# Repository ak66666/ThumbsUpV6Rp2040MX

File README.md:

# ThumbsUp! v6 RP2040-based keyboard for MX and ALPS switches

Multilevel 44 Key Split Contoured Keyboard.
2-key Thumb Cluster
   
* RP2040 is soldered on the boards.
* TRS (3-wire) audio cable to connect the halves.
* Hot swap sockets for MX switches, the ALPS need to be soldered in.
* USB-C connectors.
* Connects to computer from either side, halves could be used separately.

Board needs 3D printed switch plates: https://github.com/ak66666/ThubmsUpSwitchPlates

Other pictures in Photos folder.

# Firmware

Please refer to this article:
https://thumbsupkeyboards.blogspot.com/2024/02/source-files-and-default-firmware.html

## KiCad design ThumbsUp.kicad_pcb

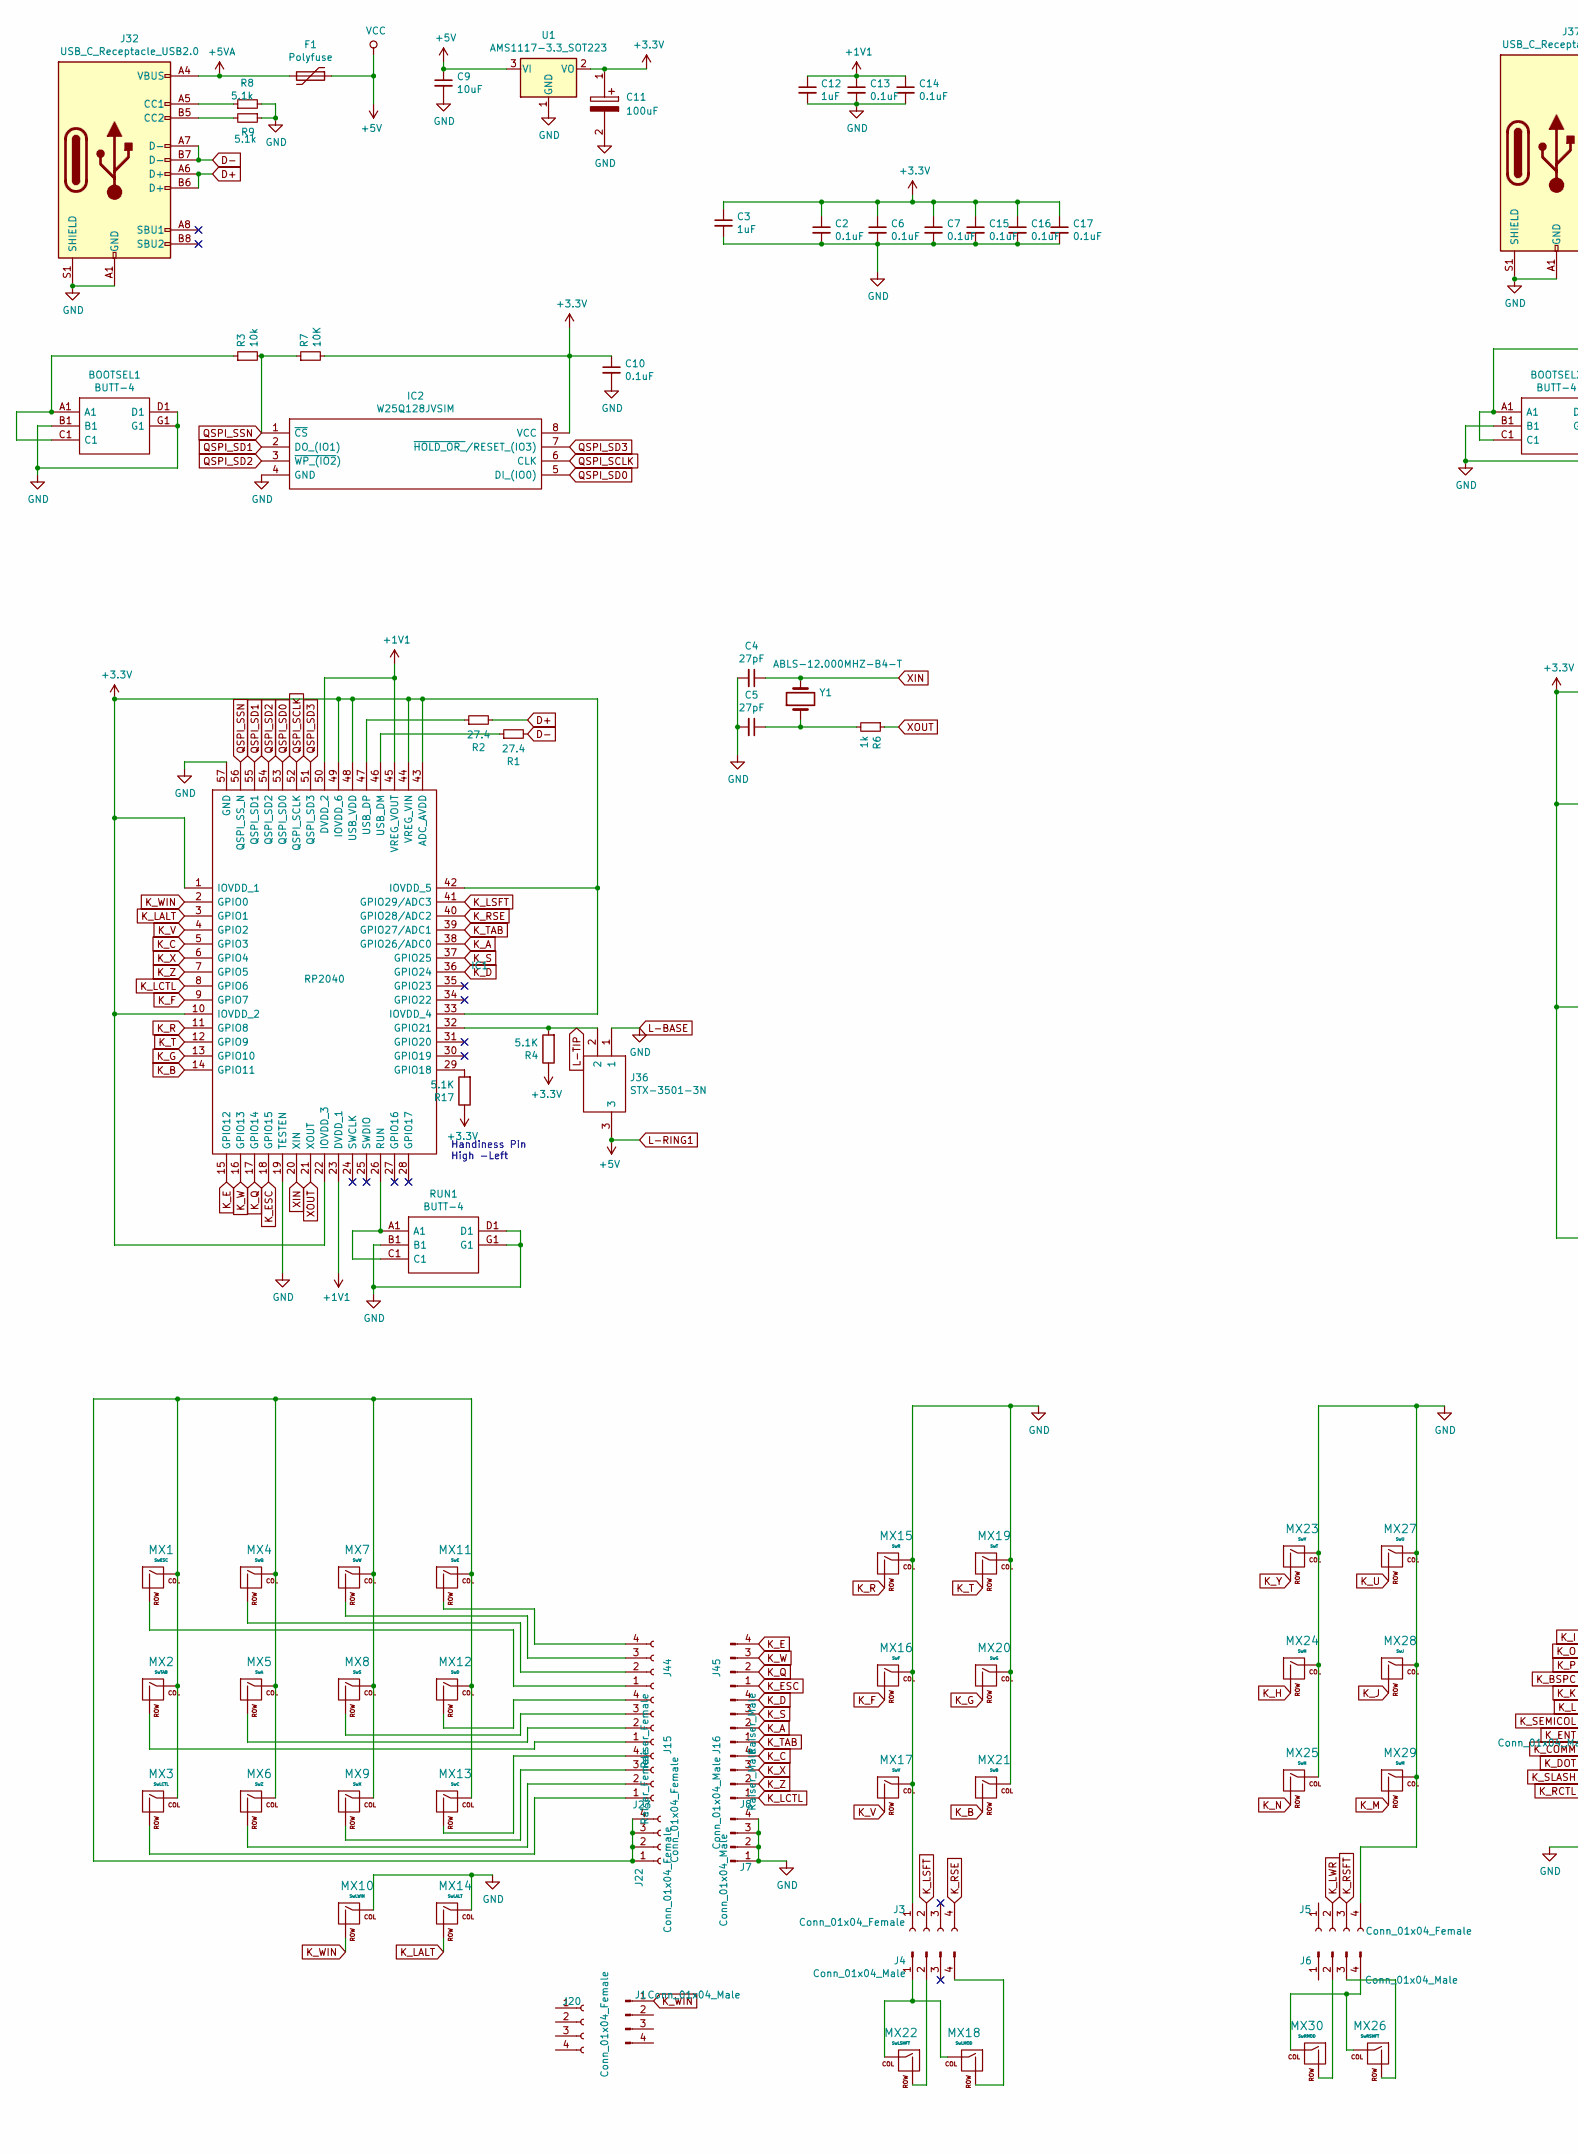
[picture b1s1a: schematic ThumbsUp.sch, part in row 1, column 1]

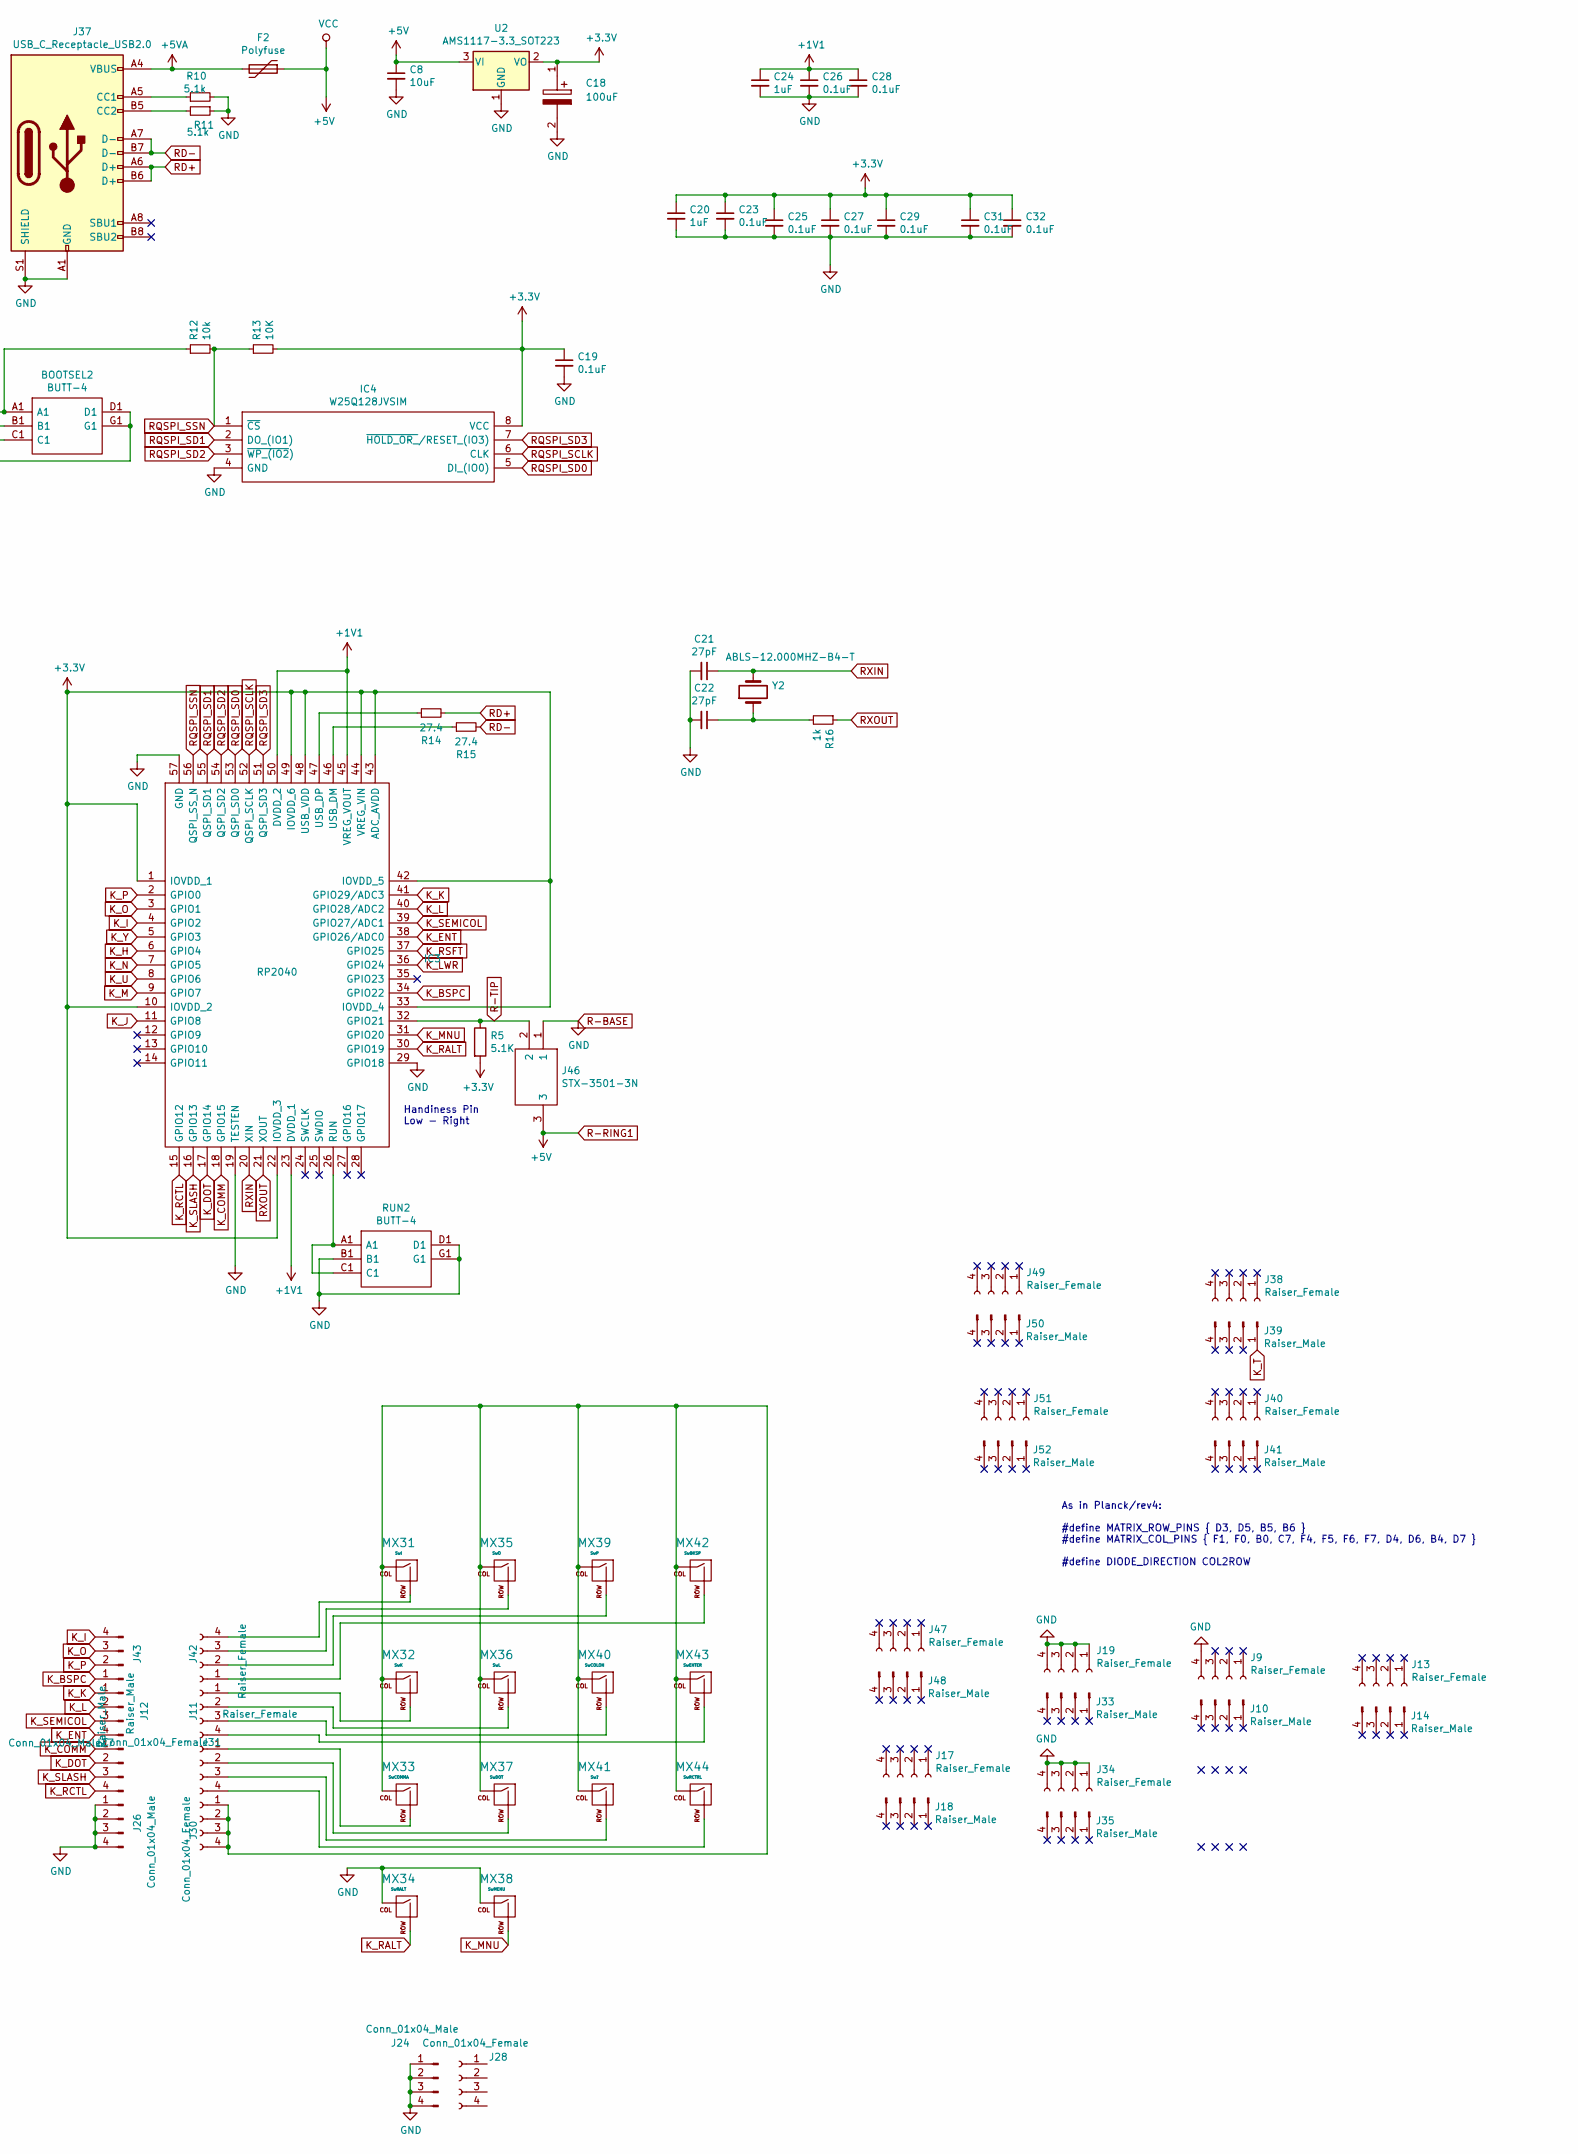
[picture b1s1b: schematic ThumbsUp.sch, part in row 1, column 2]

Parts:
BOOTSEL1, BOOTSEL2: BUTT-4; BUTT4; Manufacturer_Part_Number BUTT-4; Mouser Part Number 992-BUTT-4
C2, C6, C7, C10, C13, C14, C15, C16, C17, C19, C23, C25, C26, C27, C28, C29, C31, C32: 0.1uF; C_0402_1005Metric
C3, C12, C20, C24: 1uF; C_0402_1005Metric
C4, C5, C21, C22: 27pF; C_0402_1005Metric
C8, C9: 10uF; C_0402_1005Metric
C11, C18: 100uF; C_1210_3225Metric
F1, F2: Polyfuse; Fuse_1206_3216Metric
IC1, IC3: RP2040; RP2040-QFN-56; Manufacturer_Part_Number RP2040
IC2, IC4: W25Q128JVSIM; SOIC127P790X216-8N; Manufacturer_Part_Number W25Q128JVSIM; Mouser Part Number 454-W25Q128JVSIM
J1, J4, J6, J7, J8, J24, J26, J27: Conn_01x04_Male; PinHeader_1x04_P2.54mm_Vertical
J3, J5, J20, J22, J23, J28, J30, J31: Conn_01x04_Female; PinSocket_1x04_P2.54mm_Vertical
J9, J11, J13, J15, J17, J19, J34, J38, J40, J42, J44, J47, J49, J51: Raiser_Female; PinSocket_1x04_P2.54mm_Vertical
J10, J12, J14, J16, J18, J33, J35, J39, J41, J43, J45, J48, J50, J52: Raiser_Male; PinHeader_1x04_P2.54mm_Vertical
J32, J37: USB_C_Receptacle_USB2.0; USB_C_Receptacle_Palconn_UTC16-G
J36, J46: STX-3501-3N; STX35013N; Manufacturer_Part_Number STX-3501-3N; Mouser Part Number 806-STX-3501-3N
MX1: SwESC; MX-1U-NoLED_HotSwap
MX2: SwTAB; MX-1U-NoLED_HotSwap
MX3: SwLCTL; MX-1U-NoLED_HotSwap
MX4: SwQ; MX-1U-NoLED_HotSwap
MX5: SwA; MX-1U-NoLED_HotSwap
MX6: SwZ; MX-1U-NoLED_HotSwap
MX7: SwW; MX-1U-NoLED_HotSwap
MX8: SwS; MX-1U-NoLED_HotSwap
MX9: SwX; MX-1U-NoLED_HotSwap
MX10: SwLWIN; MX-1U-NoLED_HotSwap
MX11: SwE; MX-1U-NoLED_HotSwap
MX12: SwD; MX-1U-NoLED_HotSwap
MX13: SwC; MX-1U-NoLED_HotSwap
MX14: SwLALT; MX-1U-NoLED_HotSwap
MX15: SwR; MX-1U-NoLED_HotSwap
MX16: SwF; MX-1U-NoLED_HotSwap
MX17: SwV; MX-1U-NoLED_HotSwap
MX18: SwLMOD; MX-1U-NoLED_HotSwap
MX19: SwT; MX-1U-NoLED_HotSwap
MX20: SwG; MX-1U-NoLED_HotSwap
MX21: SwB; MX-1U-NoLED_HotSwap
MX22: SwLSHFT; MX-1U-NoLED_HotSwap
MX23: SwY; MX-1U-NoLED_HotSwap
MX24: SwH; MX-1U-NoLED_HotSwap
MX25: SwN; MX-1U-NoLED_HotSwap
MX26: SwRSHFT; MX-1U-NoLED_HotSwap
MX27: SwU; MX-1U-NoLED_HotSwap
MX28: SwJ; MX-1U-NoLED_HotSwap
MX29: SwM; MX-1U-NoLED_HotSwap
MX30: SwRMOD; MX-1U-NoLED_HotSwap
MX31: SwI; MX-1U-NoLED_HotSwap
MX32: SwK; MX-1U-NoLED_HotSwap
MX33: SwCOMMA; MX-1U-NoLED_HotSwap
MX34: SwRALT; MX-1U-NoLED_HotSwap
MX35: SwO; MX-1U-NoLED_HotSwap
MX36: SwL; MX-1U-NoLED_HotSwap
MX37: SwDOT; MX-1U-NoLED_HotSwap
MX38: SwMENU; MX-1U-NoLED_HotSwap
MX39: SwP; MX-1U-NoLED_HotSwap
MX40: SwCOLON; MX-1U-NoLED_HotSwap
MX41: Sw?; MX-1U-NoLED_HotSwap
MX42: SwBKSP; MX-1U-NoLED_HotSwap
MX43: SwENTER; MX-1U-NoLED_HotSwap
MX44: SwRCTRL; MX-1U-NoLED_HotSwap
R1, R2, R14, R15: 27.4; R_0402_1005Metric
R3, R12: 10k; R_0402_1005Metric
R4, R5, R17: 5.1K; R_0402_1005Metric
R6, R16: 1k; R_0402_1005Metric
R7, R13: 10K; R_0402_1005Metric
R8, R9, R10, R11: 5.1k; R_0402_1005Metric
RUN1, RUN2: BUTT-4; BUTT4; Manufacturer_Part_Number BUTT-4; Mouser Part Number 992-BUTT-4
U1, U2: AMS1117-3.3_SOT223; SOT229P700X180-4N
Y1, Y2: ABLS-12.000MHZ-B4-T; HC%2f49US-(AT49)_1

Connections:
+1V1: C12.1, C13.1, C14.1, C24.1, C26.1, C28.1, IC1.23 (DVDD_1), IC1.45 (VREG_VOUT), IC1.50 (DVDD_2), IC3.23 (DVDD_1), IC3.45 (VREG_VOUT), IC3.50 (DVDD_2)
+3V3: C2.1, C3.1, C6.1, C7.1, C10.1, C11.1, C15.1, C16.1, C17.1, C18.1, C19.1, C20.1, C23.1, C25.1, C27.1, C29.1, C31.1, C32.1, IC1.1 (IOVDD_1), IC1.10 (IOVDD_2), IC1.22 (IOVDD_3), IC1.33 (IOVDD_4), IC1.42 (IOVDD_5), IC1.43 (ADC_AVDD), IC1.44 (VREG_VIN), IC1.48 (USB_VDD), IC1.49 (IOVDD_6), IC2.8 (VCC), IC3.1 (IOVDD_1), IC3.10 (IOVDD_2), IC3.22 (IOVDD_3), IC3.33 (IOVDD_4), IC3.42 (IOVDD_5), IC3.43 (ADC_AVDD), IC3.44 (VREG_VIN), IC3.48 (USB_VDD), IC3.49 (IOVDD_6), IC4.8 (VCC), R4.1, R5.2, R7.2, R13.2, R17.1, U1.2 (VO), U2.2 (VO)
+5VA: F1.2, F2.2, J32.A4 (VBUS), J32.A9 (VBUS), J32.B4 (VBUS), J32.B9 (VBUS), J37.A4 (VBUS), J37.A9 (VBUS), J37.B4 (VBUS), J37.B9 (VBUS)
D+: J32.A6 (D+), J32.B6 (D+), R2.2
D-: J32.A7 (D-), J32.B7 (D-), R1.2
K_A: IC1.38 (GPIO26/ADC0), J16.2
K_B: IC1.14 (GPIO11), MX21.2 (ROW)
K_BSPC: IC3.34 (GPIO22), J43.1
K_C: IC1.5 (GPIO3), J8.4
K_COMM: IC3.18 (GPIO15), J27.1
K_D: IC1.36 (GPIO24), J16.4
K_DOT: IC3.17 (GPIO14), J27.2
K_E: IC1.15 (GPIO12), J45.4
K_ENT: IC3.38 (GPIO26/ADC0), J12.4
K_ESC: IC1.18 (GPIO15), J45.1
K_F: IC1.9 (GPIO7), MX16.2 (ROW)
K_G: IC1.13 (GPIO10), MX20.2 (ROW)
K_H: IC3.6 (GPIO4), MX24.2 (ROW)
K_I: IC3.4 (GPIO2), J43.4
K_J: IC3.11 (GPIO8), MX28.2 (ROW)
K_K: IC3.41 (GPIO29/ADC3), J12.1
K_L: IC3.40 (GPIO28/ADC2), J12.2
K_LALT: IC1.3 (GPIO1), MX14.2 (ROW)
K_LCTL: IC1.8 (GPIO6), J8.1
K_LSFT: IC1.41 (GPIO29/ADC3), J3.2
K_LWR: IC3.36 (GPIO24), J5.2
K_M: IC3.9 (GPIO7), MX29.2 (ROW)
K_MNU: IC3.31 (GPIO20), MX38.2 (ROW)
K_N: IC3.7 (GPIO5), MX25.2 (ROW)
K_O: IC3.3 (GPIO1), J43.3
K_P: IC3.2 (GPIO0), J43.2
K_Q: IC1.17 (GPIO14), J45.2
K_R: IC1.11 (GPIO8), MX15.2 (ROW)
K_RALT: IC3.30 (GPIO19), MX34.2 (ROW)
K_RCTL: IC3.15 (GPIO12), J27.4
K_RSE: IC1.40 (GPIO28/ADC2), J3.4
K_RSFT: IC3.37 (GPIO25), J5.3
K_S: IC1.37 (GPIO25), J16.3
K_SEMICOL: IC3.39 (GPIO27/ADC1), J12.3
K_SLASH: IC3.16 (GPIO13), J27.3
K_T: IC1.12 (GPIO9), J39.1, MX19.2 (ROW)
K_TAB: IC1.39 (GPIO27/ADC1), J16.1
K_U: IC3.8 (GPIO6), MX27.2 (ROW)
K_V: IC1.4 (GPIO2), MX17.2 (ROW)
K_W: IC1.16 (GPIO13), J45.3
K_WIN: IC1.2 (GPIO0), J1.1, MX10.2 (ROW)
K_X: IC1.6 (GPIO4), J8.3
K_Y: IC3.5 (GPIO3), MX23.2 (ROW)
K_Z: IC1.7 (GPIO5), J8.2
L-BASE: BOOTSEL1.B1, BOOTSEL1.D1, BOOTSEL1.G1, BOOTSEL2.B1, BOOTSEL2.D1, BOOTSEL2.G1, C2.2, C3.2, C4.2, C5.2, C6.2, C7.2, C8.2, C9.2, C10.2, C11.2, C12.2, C13.2, C14.2, C15.2, C16.2, C17.2, C18.2, C19.2, C20.2, C21.2, C22.2, C23.2, C24.2, C25.2, C26.2, C27.2, C28.2, C29.2, C31.2, C32.2, IC1.19 (TESTEN), IC1.57 (GND), IC2.4 (GND), IC3.19 (TESTEN), IC3.29 (GPIO18), IC3.57 (GND), IC4.4 (GND), J3.1, J5.4, J7.1, J7.2, J7.3, J7.4, J9.4, J19.1, J19.2, J19.3, J19.4, J24.1, J24.2, J24.3, J24.4, J26.1, J26.2, J26.3, J26.4, J32.A1 (GND), J32.A12 (GND), J32.B1 (GND), J32.B12 (GND), J32.S1 (SHIELD), J34.1, J34.2, J34.3, J34.4, J36.1, J37.A1 (GND), J37.A12 (GND), J37.B1 (GND), J37.B12 (GND), J37.S1 (SHIELD), J46.1, MX10.1 (COL), MX14.1 (COL), MX15.1 (COL), MX16.1 (COL), MX17.1 (COL), MX19.1 (COL), MX20.1 (COL), MX21.1 (COL), MX23.1 (COL), MX24.1 (COL), MX25.1 (COL), MX27.1 (COL), MX28.1 (COL), MX29.1 (COL), MX34.1 (COL), MX38.1 (COL), R8.2, R9.1, R10.2, R11.1, RUN1.B1, RUN1.D1, RUN1.G1, RUN2.B1, RUN2.D1, RUN2.G1, U1.1 (GND), U2.1 (GND)
L-RING1: C8.1, C9.1, F1.1, F2.1, J36.3, J46.3, U1.3 (VI), U2.3 (VI)
L-TIP: IC1.32 (GPIO21), J36.2, R4.2
unnamed: BOOTSEL1.A1, BOOTSEL1.C1, R3.1
unnamed: BOOTSEL2.A1, BOOTSEL2.C1, R12.1
unnamed: C5.1, R6.2, Y1.1
unnamed: C22.1, R16.2, Y2.1
unnamed: IC1.26 (RUN), RUN1.A1, RUN1.C1
unnamed: IC1.29 (GPIO18), R17.2
unnamed: IC1.46 (USB_DM), R1.1
unnamed: IC1.47 (USB_DP), R2.1
unnamed: IC3.26 (RUN), RUN2.A1, RUN2.C1
unnamed: IC3.46 (USB_DM), R15.1
unnamed: IC3.47 (USB_DP), R14.1
unnamed: J4.1, MX18.1 (COL), MX22.1 (COL)
unnamed: J4.2, MX22.2 (ROW)
unnamed: J4.4, MX18.2 (ROW)
unnamed: J6.2, MX30.2 (ROW)
unnamed: J6.3, MX26.2 (ROW)
unnamed: J6.4, MX26.1 (COL), MX30.1 (COL)
unnamed: J11.1, MX32.2 (ROW)
unnamed: J11.2, MX36.2 (ROW)
unnamed: J11.3, MX40.2 (ROW)
unnamed: J11.4, MX43.2 (ROW)
unnamed: J15.1, MX2.2 (ROW)
unnamed: J15.2, MX5.2 (ROW)
unnamed: J15.3, MX8.2 (ROW)
unnamed: J15.4, MX12.2 (ROW)
unnamed: J22.1, J22.2, J22.3, J22.4, MX1.1 (COL), MX2.1 (COL), MX3.1 (COL), MX4.1 (COL), MX5.1 (COL), MX6.1 (COL), MX7.1 (COL), MX8.1 (COL), MX9.1 (COL), MX11.1 (COL), MX12.1 (COL), MX13.1 (COL)
unnamed: J23.1, MX3.2 (ROW)
unnamed: J23.2, MX6.2 (ROW)
unnamed: J23.3, MX9.2 (ROW)
unnamed: J23.4, MX13.2 (ROW)
unnamed: J30.1, J30.2, J30.3, J30.4, MX31.1 (COL), MX32.1 (COL), MX33.1 (COL), MX35.1 (COL), MX36.1 (COL), MX37.1 (COL), MX39.1 (COL), MX40.1 (COL), MX41.1 (COL), MX42.1 (COL), MX43.1 (COL), MX44.1 (COL)
unnamed: J31.1, MX33.2 (ROW)
unnamed: J31.2, MX37.2 (ROW)
unnamed: J31.3, MX41.2 (ROW)
unnamed: J31.4, MX44.2 (ROW)
unnamed: J32.A5 (CC1), R8.1
unnamed: J32.B5 (CC2), R9.2
unnamed: J37.A5 (CC1), R10.1
unnamed: J37.B5 (CC2), R11.2
unnamed: J42.1, MX42.2 (ROW)
unnamed: J42.2, MX39.2 (ROW)
unnamed: J42.3, MX35.2 (ROW)
unnamed: J42.4, MX31.2 (ROW)
unnamed: J44.1, MX1.2 (ROW)
unnamed: J44.2, MX4.2 (ROW)
unnamed: J44.3, MX7.2 (ROW)
unnamed: J44.4, MX11.2 (ROW)
QSPI_SCLK: IC1.52 (QSPI_SCLK), IC2.6 (CLK)
QSPI_SD0: IC1.53 (QSPI_SD0), IC2.5 (DI_(IO0))
QSPI_SD1: IC1.55 (QSPI_SD1), IC2.2 (DO_(IO1))
QSPI_SD2: IC1.54 (QSPI_SD2), IC2.3 (~WP_(IO2))
QSPI_SD3: IC1.51 (QSPI_SD3), IC2.7 (~HOLD_OR_~/RESET_(IO3))
QSPI_SSN: IC1.56 (QSPI_SS_N), IC2.1 (~CS), R3.2, R7.1
R-TIP: IC3.32 (GPIO21), J46.2, R5.1
RD+: J37.A6 (D+), J37.B6 (D+), R14.2
RD-: J37.A7 (D-), J37.B7 (D-), R15.2
RQSPI_SCLK: IC3.52 (QSPI_SCLK), IC4.6 (CLK)
RQSPI_SD0: IC3.53 (QSPI_SD0), IC4.5 (DI_(IO0))
RQSPI_SD1: IC3.55 (QSPI_SD1), IC4.2 (DO_(IO1))
RQSPI_SD2: IC3.54 (QSPI_SD2), IC4.3 (~WP_(IO2))
RQSPI_SD3: IC3.51 (QSPI_SD3), IC4.7 (~HOLD_OR_~/RESET_(IO3))
RQSPI_SSN: IC3.56 (QSPI_SS_N), IC4.1 (~CS), R12.2, R13.1
RXIN: C21.1, IC3.20 (XIN), Y2.2
RXOUT: IC3.21 (XOUT), R16.1
XIN: C4.1, IC1.20 (XIN), Y1.2
XOUT: IC1.21 (XOUT), R6.1

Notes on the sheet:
As in Planck/rev4: #define MATRIX_ROW_PINS { D3, D5, B5, B6 } #define MATRIX_COL_PINS { F1, F0, B0, C7, F4, F5, F6, F7, D4, D6, B4, D7 } #define DIODE_DIRECTION COL2ROW
Handiness Pin High -Left
Handiness Pin Low - Right

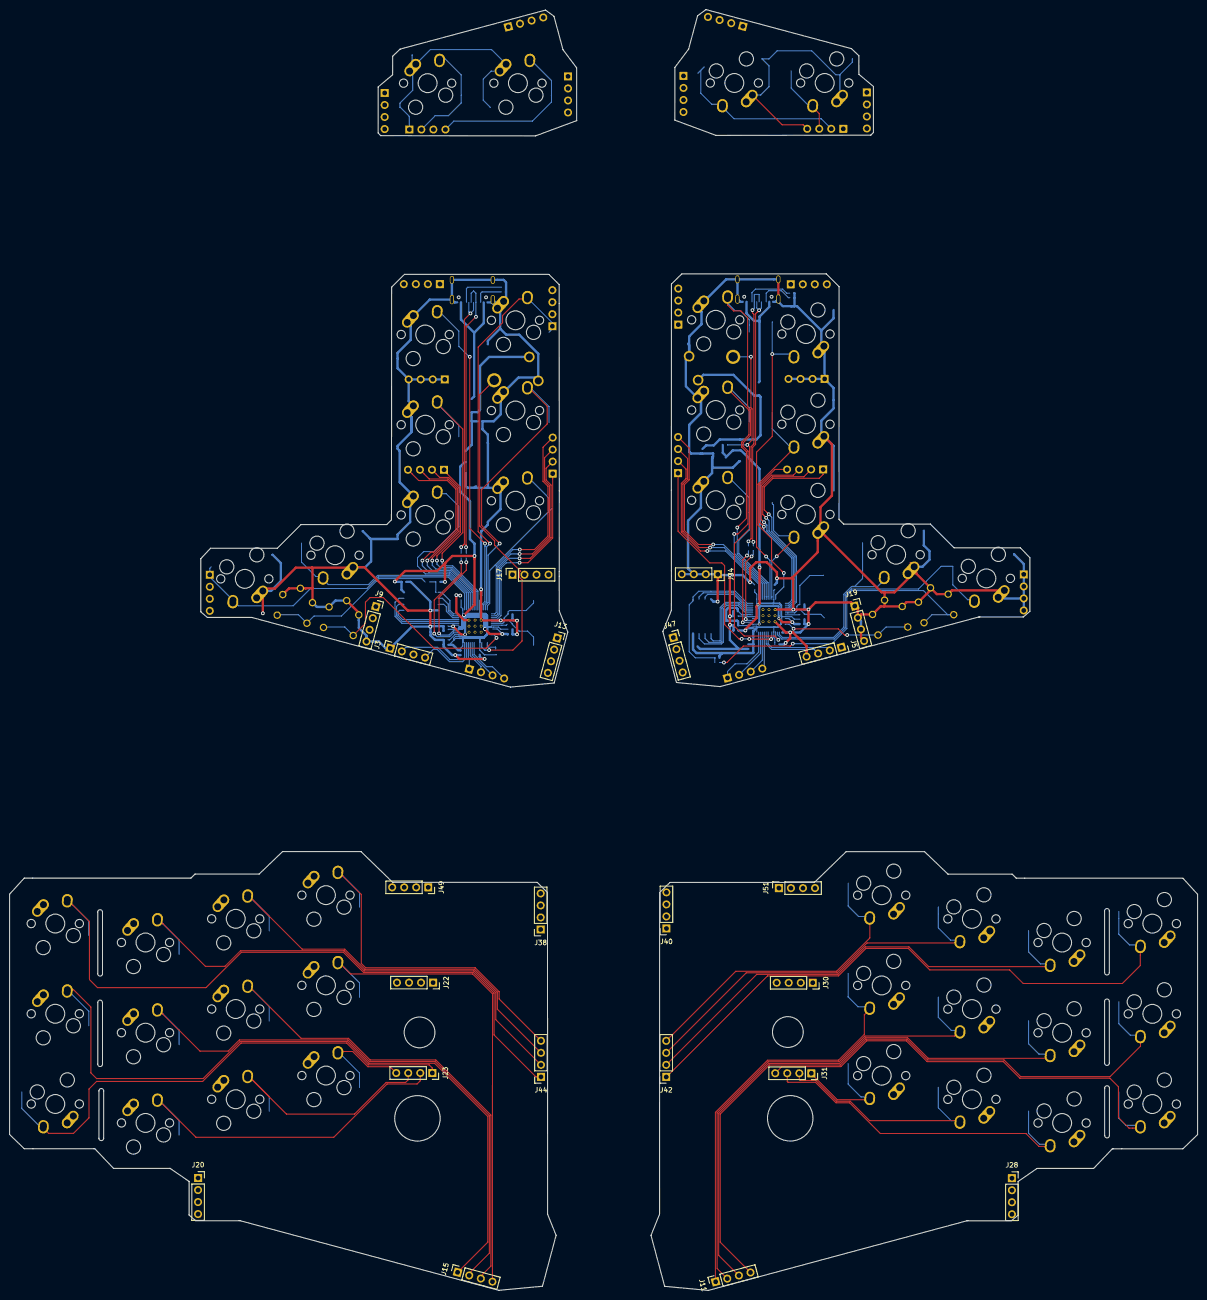
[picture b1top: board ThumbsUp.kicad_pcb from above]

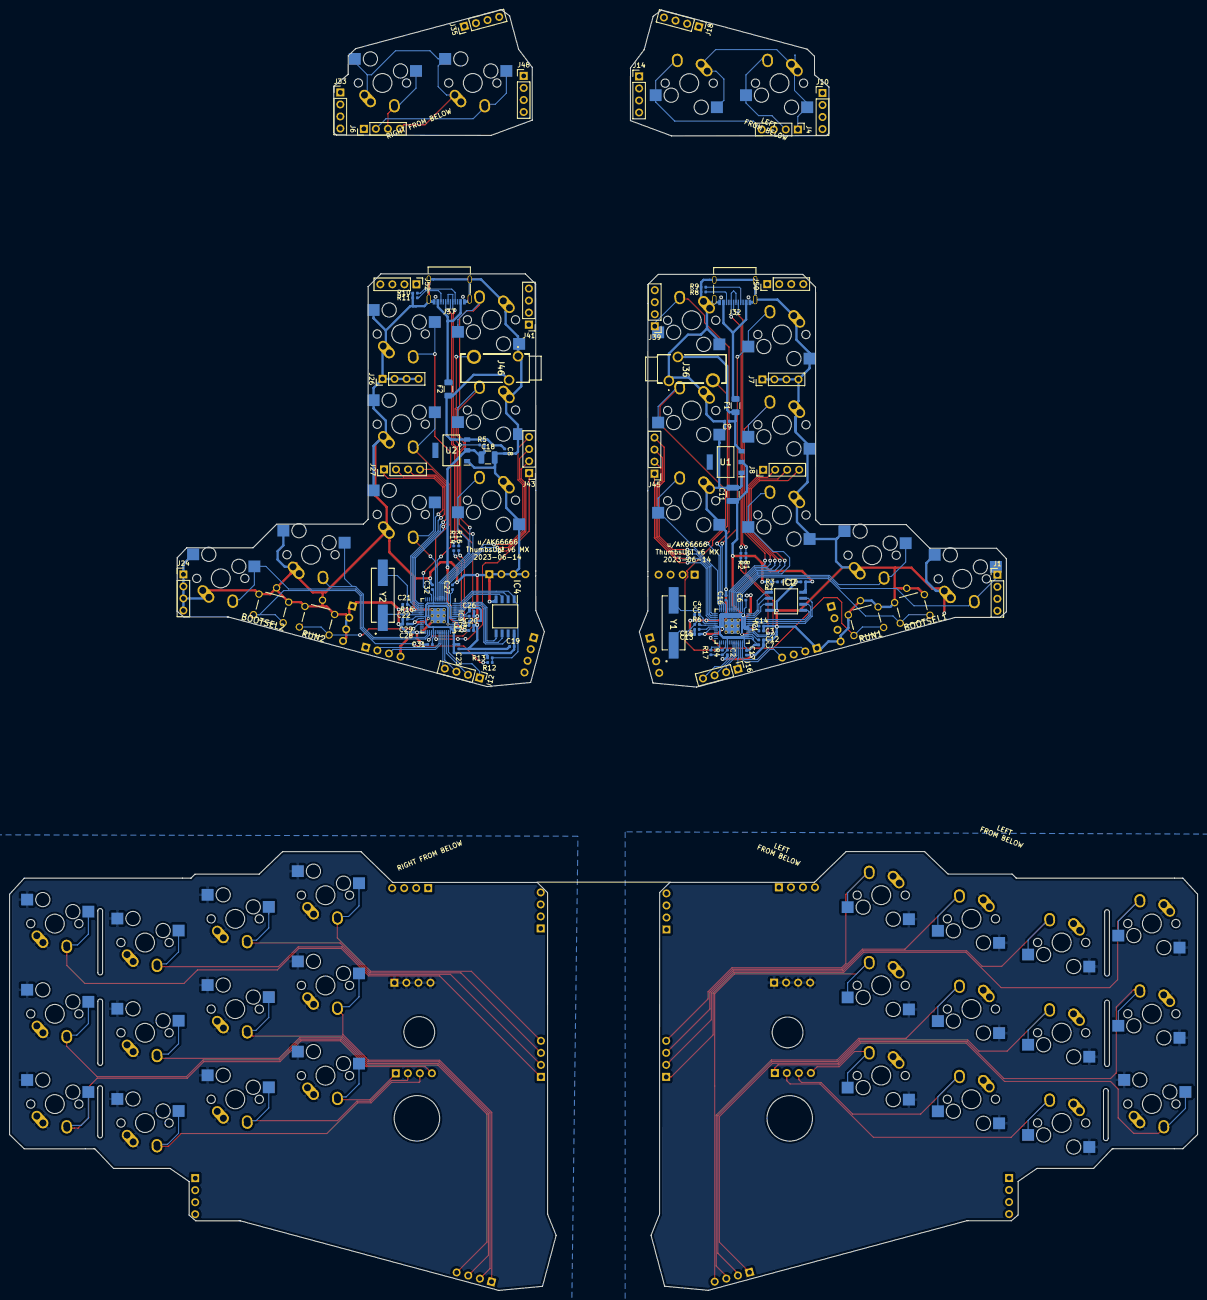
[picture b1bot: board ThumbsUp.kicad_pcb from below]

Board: 2 copper layers, 250.8 x 270.5 mm, 153 parts (87 on the bottom side), 118 nets.

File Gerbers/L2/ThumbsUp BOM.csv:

"Id";"Designator";"Package";"Quantity";"Designation";"Supplier and ref";
1;"G***";"LeavesW311";1;"LOGO";;;
2;"MX20";"MX-1U-NoLED_HotSwap";1;"SwG";;;
3;"U1";"SOT229P700X180-4N";1;"AMS1117-3.3_SOT223";;;
4;"C11";"C_1210_3225Metric";1;"100uF";;;
5;"RUN1,BOOTSEL1";"BUTT4";2;"BUTT-4";;;
6;"R17,R4";"R_0402_1005Metric";2;"5.1K";;;
7;"J50,J39,J45,J16";"PinHeader_1x04_P2.54mm_Vertical";4;"Raiser_Male";;;
8;"MX16";"MX-1U-NoLED_HotSwap";1;"SwF";;;
9;"MX21";"MX-1U-NoLED_HotSwap";1;"SwB";;;
10;"MX19";"MX-1U-NoLED_HotSwap";1;"SwT";;;
11;"MX17";"MX-1U-NoLED_HotSwap";1;"SwV";;;
12;"MX15";"MX-1U-NoLED_HotSwap";1;"SwR";;;
13;"MX14";"MX-1U-NoLED_HotSwap";1;"SwLALT";;;
14;"MX10";"MX-1U-NoLED_HotSwap";1;"SwLWIN";;;
15;"R2,R1";"R_0402_1005Metric";2;"27.4";;;
16;"R9,R8";"R_0402_1005Metric";2;"5.1k";;;
17;"R7";"R_0402_1005Metric";1;"10K";;;
18;"R6";"R_0402_1005Metric";1;"1k";;;
19;"R3";"R_0402_1005Metric";1;"10k";;;
20;"C17,C16,C15,C14,C13,C10,C7,C6,C2";"C_0402_1005Metric";9;"0.1uF";;;
21;"C12,C3";"C_0402_1005Metric";2;"1uF";;;
22;"C9";"C_0402_1005Metric";1;"10uF";;;
23;"C5,C4";"C_0402_1005Metric";2;"27pF";;;
24;"J32";"USB_C_Receptacle_Palconn_UTC16-G";1;"USB_C_Receptacle_USB2.0";;;
25;"J3";"PinSocket_1x04_P2.54mm_Vertical";1;"Conn_01x04_Female";;;
26;"J36";"STX35013N";1;"STX-3501-3N";;;
27;"J17,J9,J13";"PinSocket_1x04_P2.54mm_Vertical";3;"Raiser_Female";;;
28;"J1,J8,J7";"PinHeader_1x04_P2.54mm_Vertical";3;"Conn_01x04_Male";;;
29;"Y1";"HC%2f49US-(AT49)_1";1;"ABLS-12.000MHZ-B4-T";;;
30;"IC2";"SOIC127P790X216-8N";1;"W25Q128JVSIM";;;
31;"IC1";"QFN40P700X700X90-57N-D";1;"RP2040";;;
32;"F1";"Fuse_1206_3216Metric";1;"Polyfuse";;;

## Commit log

2023-06-15 Initial check-in of v6
2023-06-15 Removed the top row in schematics and PCBs, redrew the tracks
2023-06-17 Added new silkscreen, trying to apply it.
2023-06-18 Joined the L2 and R2 to save on setting up.
2023-06-18 Reverted the joining step - made the L2 and R2 separate again. The LR2 gerbers and PCB files are still there, so may return to this idea later on.
2023-07-19 Re-wired L2 RP2040 and memory as per manual
2023-07-19 Re-wired R2 RP2040 and memory as per manual
2023-07-21 Re-wired R2 RP2040 - moved the R, C around it.
2023-07-28 Fixed tracks too close to vias, applied silkscreen to Level 2
2023-07-28 Renerated Gerbers, POS, BOMs for Level 2
2023-08-03 Re-defined POS, BOMs for Level 2, as ordered on 20230803
2025-02-27 ThumbsUp v6: Updated description.
